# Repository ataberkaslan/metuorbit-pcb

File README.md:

# METUORBIT PCB Design
Created by [Ataberk ASLAN](https://github.com/ataberkaslan)
## License
This project is licensed under [Apache 2.0](https://www.apache.org/licenses/LICENSE-2.0)

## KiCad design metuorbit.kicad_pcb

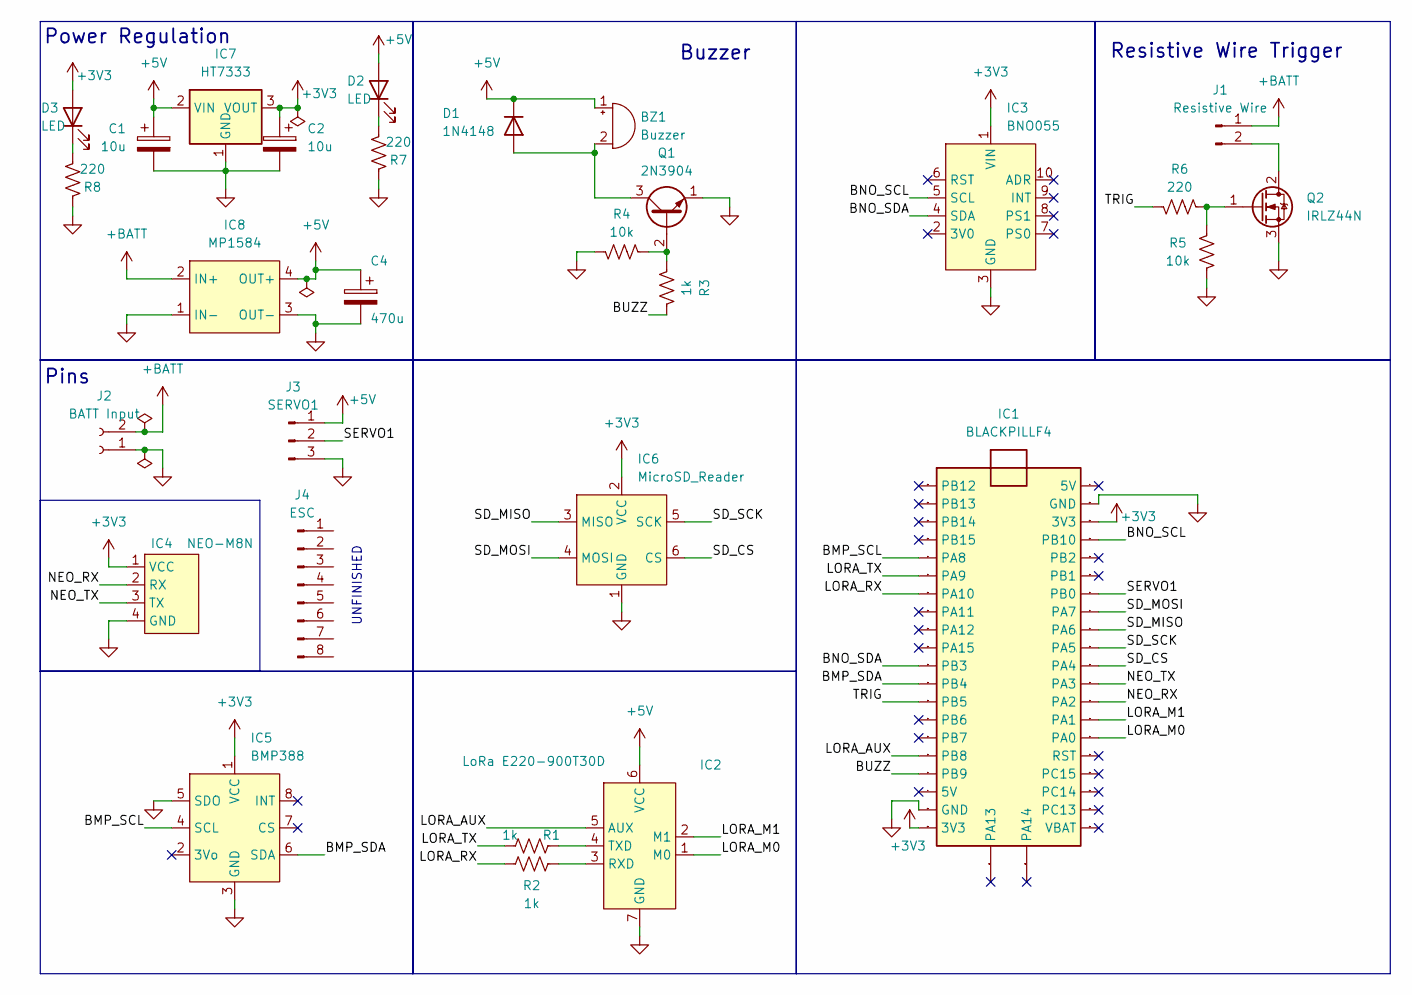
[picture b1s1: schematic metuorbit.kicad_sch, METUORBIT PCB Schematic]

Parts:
BZ1: Buzzer; Buzzer_12x9.5RM7.6
C1, C2: 10u; CP_Radial_D5.0mm_P2.50mm
C4: 470u; CP_Radial_D8.0mm_P3.50mm
D1: 1N4148; D_DO-35_SOD27_P7.62mm_Horizontal
D2, D3: LED; LED_1206_3216Metric_Pad1.42x1.75mm_HandSolder
IC1: BLACKPILLF4; Manufacturer Part BlackPill
IC2: LoRa E220-900T30D; MESHNODES-E220-900T30D+22D
IC3: BNO055
IC4: NEO-M8N
IC5: BMP388
IC6: MicroSD_Reader; MicroSD Reader
IC7: HT7333; TO-92
IC8: MP1584
J1: Resistive Wire; TerminalBlock_Phoenix_MKDS-1,5-2-5.08_1x02_P5.08mm_Horizont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
J2: BATT Input; SolderWire-6sqmm_1x02_P14mm_D3.5mm_OD7mm
J3: SERVO1; PinHeader_1x03_P2.54mm_Vertical
J4: ESC
Q1: 2N3904; TO-92_Inline
Q2: IRLZ44N; TO-220-3_Vertical
R1, R2, R3: 1k; R_1206_3216Metric_Pad1.30x1.75mm_HandSolder
R4, R5: 10k; R_1206_3216Metric_Pad1.30x1.75mm_HandSolder
R6, R7, R8: 220; R_1206_3216Metric_Pad1.30x1.75mm_HandSolder

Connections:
+3V3: C2.1, D3.2 (A), IC1.3V3_1 (3V3), IC1.3V3_2 (3V3), IC3.1 (VIN), IC4.1 (VCC), IC5.1 (VCC), IC6.2 (VCC), IC7.3 (VOUT)
+5V: BZ1.1 (+), C1.1, C4.1, D1.1 (K), D2.2 (A), IC2.6 (VCC), IC7.2 (VIN), IC8.4 (OUT+), J3.1
+BATT: IC8.2 (IN+), J1.1, J2.2
/BMP_SCL: IC1.PA8, IC5.4 (SCL)
/BMP_SDA: IC1.PB4, IC5.6 (SDA)
/BNO_SCL: IC1.PB10, IC3.5 (SCL)
/BNO_SDA: IC1.PB3, IC3.4 (SDA)
/BUZZ: IC1.PB9, R3.1
/LORA_AUX: IC1.PB8, IC2.5 (AUX)
/LORA_M0: IC1.PA0, IC2.1 (M0)
/LORA_M1: IC1.PA1, IC2.2 (M1)
/LORA_RX: IC1.PA10, R2.1
/LORA_TX: IC1.PA9, R1.1
/NEO_RX: IC1.PA2, IC4.2 (RX)
/NEO_TX: IC1.PA3, IC4.3 (TX)
/SD_CS: IC1.PA4, IC6.6 (CS)
/SD_MISO: IC1.PA6, IC6.3 (MISO)
/SD_MOSI: IC1.PA7, IC6.4 (MOSI)
/SD_SCK: IC1.PA5, IC6.5 (SCK)
/SERVO1: IC1.PB0, J3.2
/TRIG: IC1.PB5, R6.2
GND: C1.2, C2.2, C4.2, IC1.GND_1 (GND), IC1.GND_3 (GND), IC2.7 (GND), IC3.3 (GND), IC4.4 (GND), IC5.3 (GND), IC5.5 (SDO), IC6.1 (GND), IC7.1 (GND), IC8.1 (IN-), IC8.3 (OUT-), J2.1, J3.3, Q1.1 (E), Q2.3 (S), R4.2, R5.2, R7.2, R8.2
unnamed: BZ1.2 (-), D1.2 (A), Q1.3 (C)
unnamed: D2.1 (K), R7.1
unnamed: D3.1 (K), R8.1
unnamed: IC2.3 (RXD), R2.2
unnamed: IC2.4 (TXD), R1.2
unnamed: J1.2, Q2.2 (D)
unnamed: Q1.2 (B), R3.2, R4.1
unnamed: Q2.1 (G), R5.1, R6.1

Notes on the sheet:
Power Regulation
UNFINISHED
Buzzer
Pins
Resistive Wire Trigger

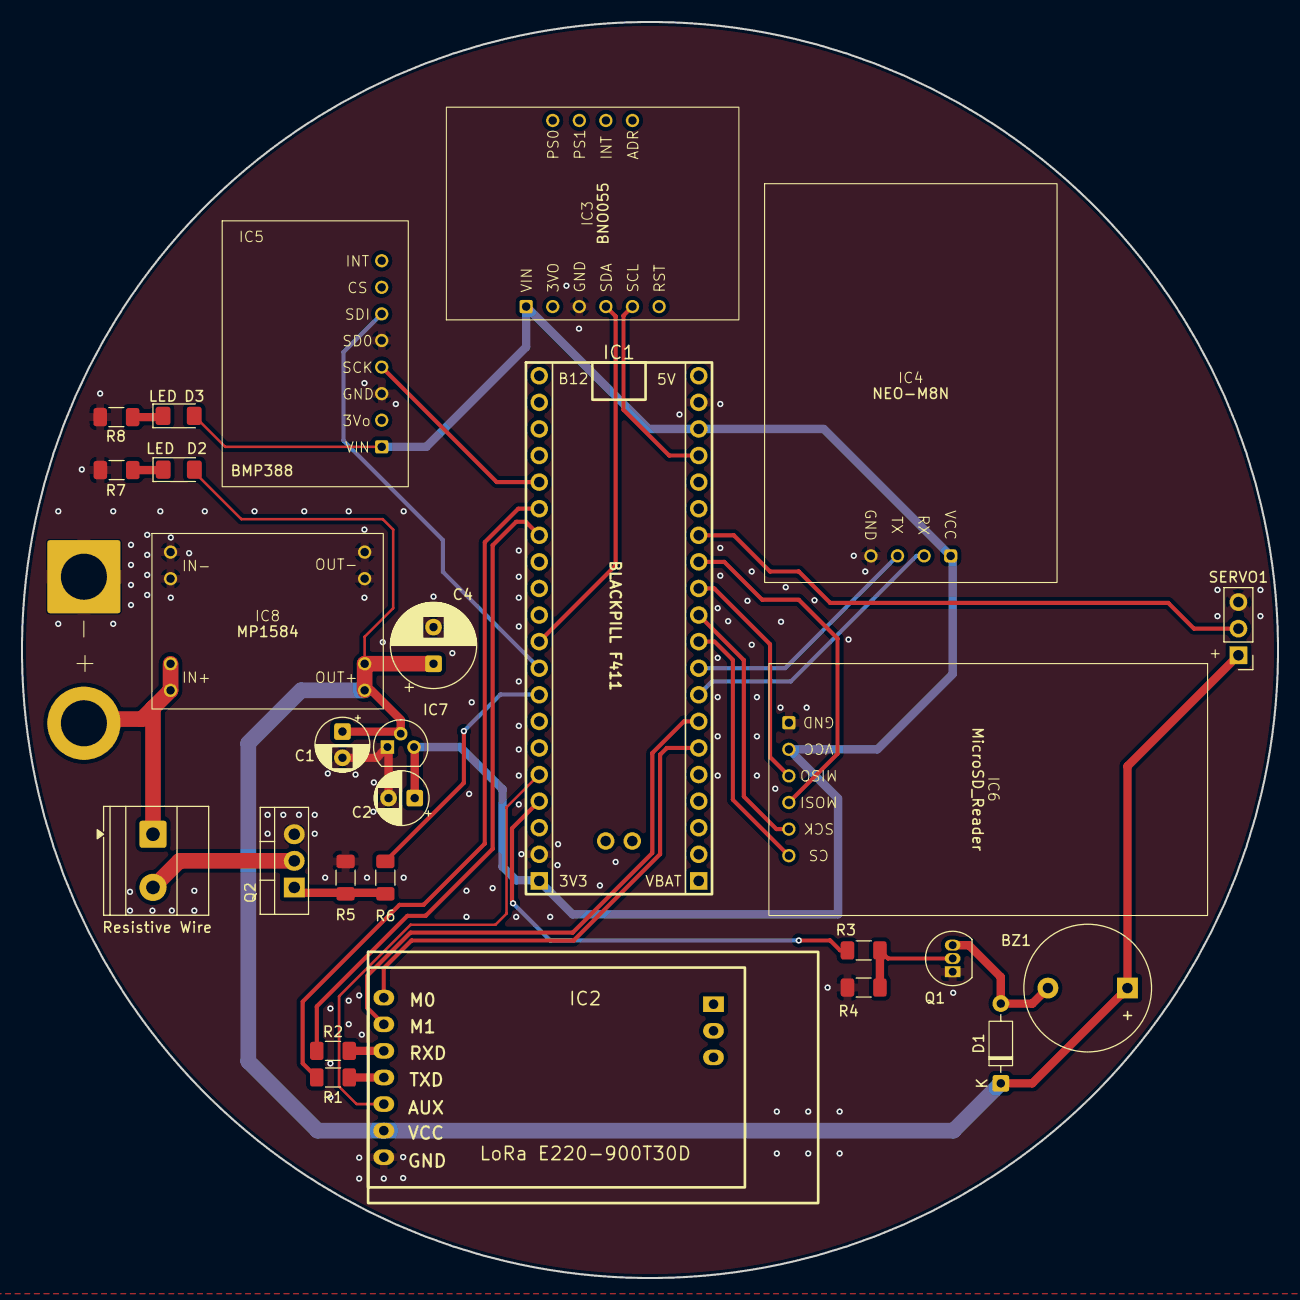
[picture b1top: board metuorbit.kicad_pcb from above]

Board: 2 copper layers, 120.0 x 120.0 mm, 28 parts (0 on the bottom side), 30 nets.
